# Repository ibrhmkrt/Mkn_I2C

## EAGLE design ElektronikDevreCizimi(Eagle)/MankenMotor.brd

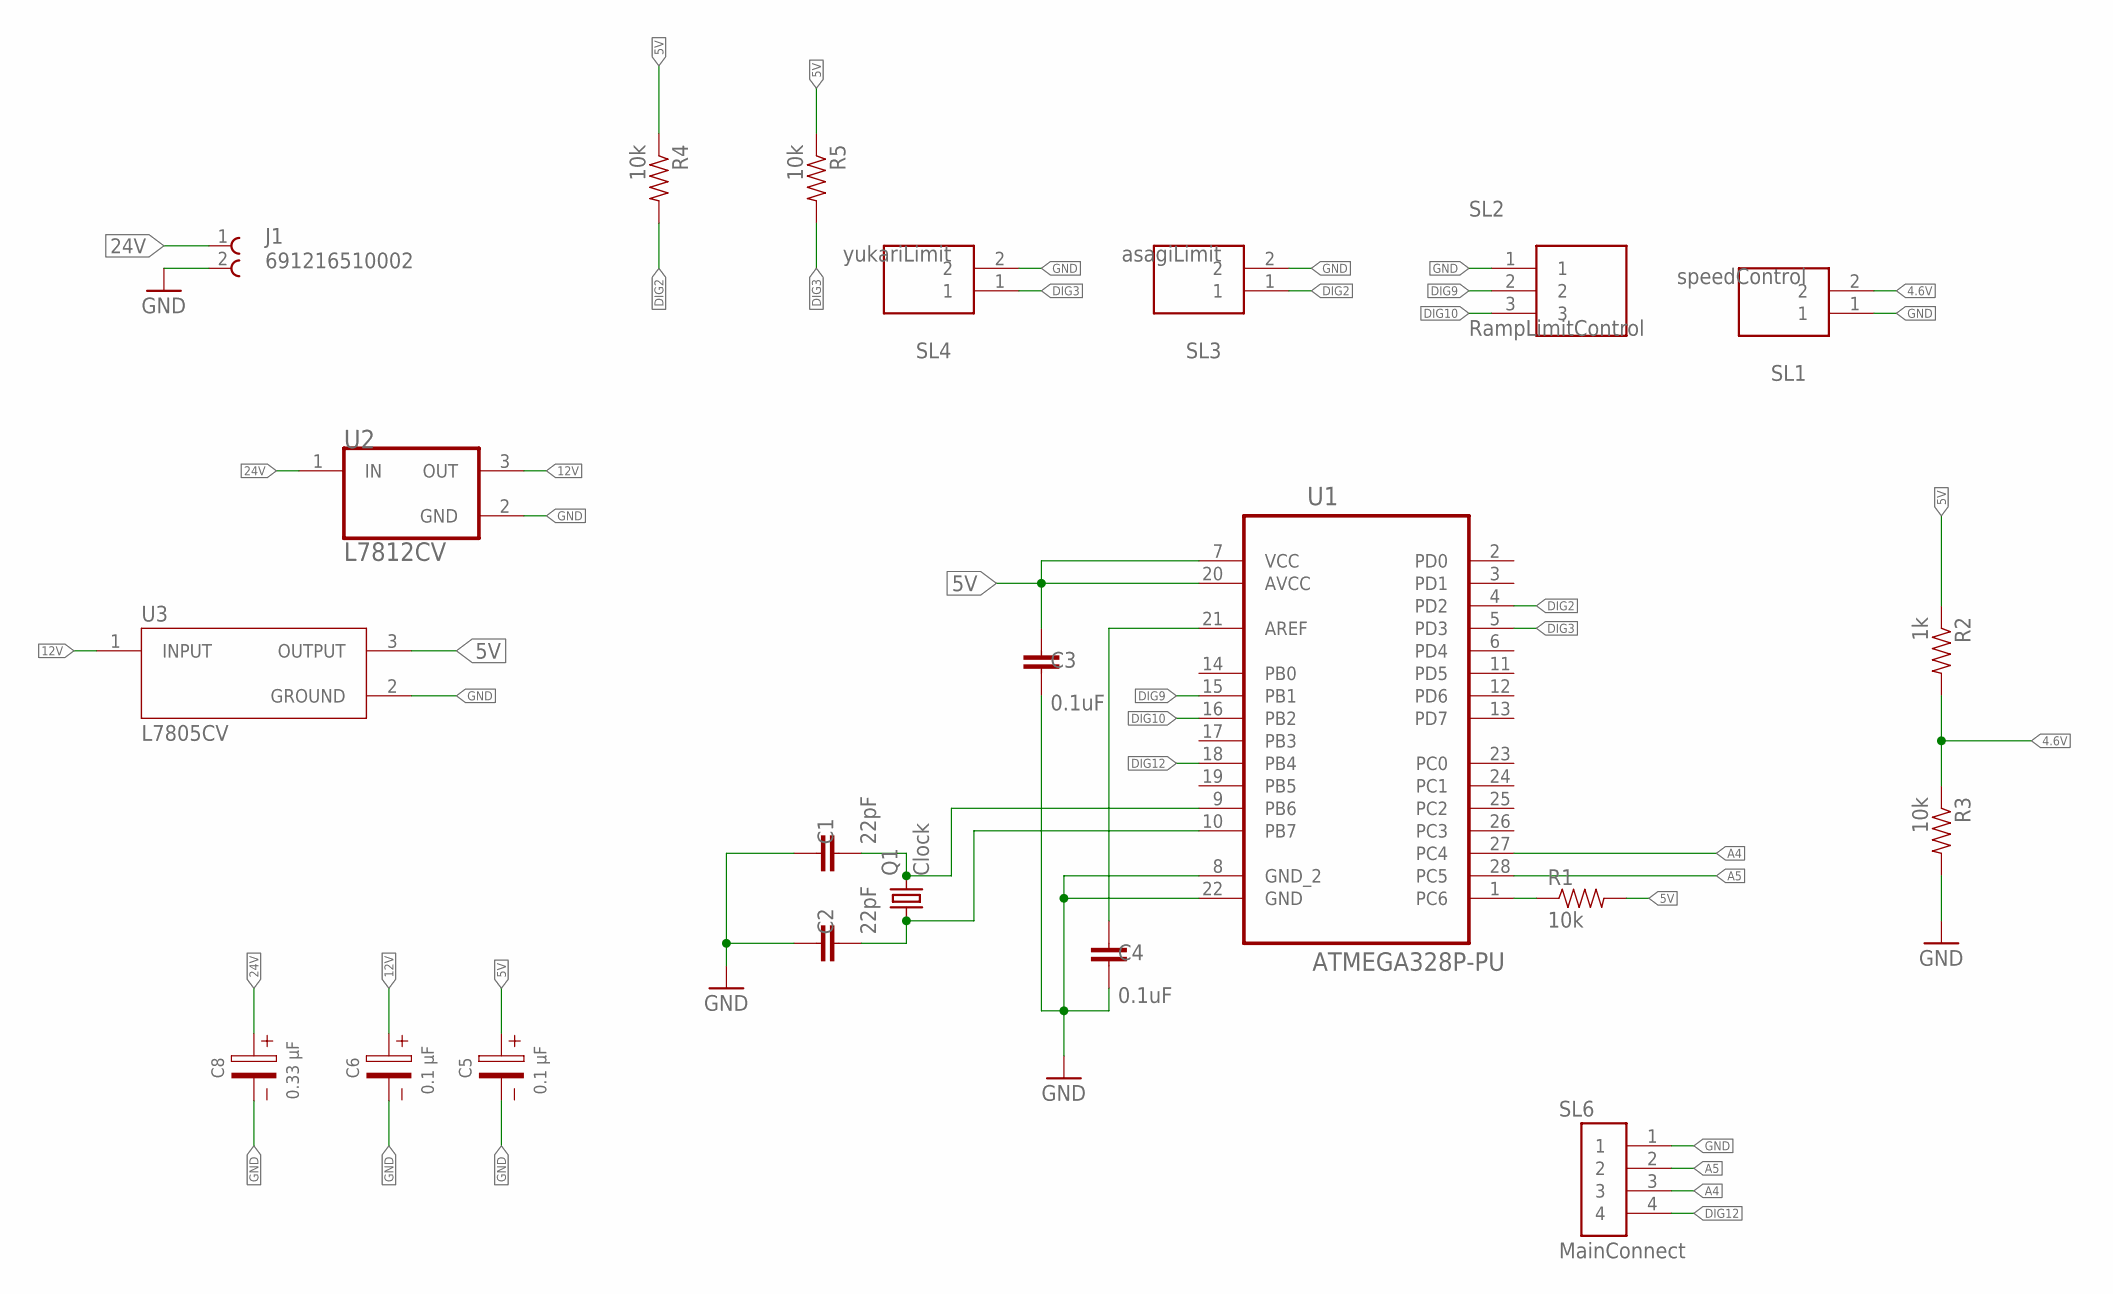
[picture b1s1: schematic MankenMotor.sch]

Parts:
C1, C2: 22pF; CAP-PTH-2.54
C3, C4: 0.1uF; CAP-PTH-SMALL-KIT
C5, C6: 0.1 µF; WCAP-ATG5_5X11(DXL)
C8: 0.33 µF; WCAP-ATG5_5X11(DXL)
J1: 691216510002
Q1: Clock; HC49/S
R1, R3, R4, R5: 10k; AXIAL-0.3
R2: 1k; AXIAL-0.3
SL1: speedControl; JST_B2B-XH-A(LF)(SN)
SL2: RampLimitControl; SHDR3W64P0X250_1X3_990X575X700
SL3: asagiLimit; JST_B2B-XH-A(LF)(SN)
SL4: yukariLimit; JST_B2B-XH-A(LF)(SN)
SL6: MainConnect; JST_B4B-XH-A(LF)(SN)
U1: ATMEGA328P-PU; DIP254P762X457-28
U2: L7812CV; TO-220-3
U3: L7805CV; TO255P1040X460X1968-3

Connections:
4.6V: R2.P$2 (2), R3.P$1 (1), SL1.2
5V: C3.1, C5.1 (+), R1.P$2 (2), R2.P$1 (1), R4.P$1 (1), R5.P$1 (1), U1.7 (VCC), U1.20 (AVCC), U3.3 (OUTPUT)
12V: C6.1 (+), U2.3 (OUT), U3.1 (INPUT)
24V: C8.1 (+), J1.1, U2.1 (IN)
A4: SL6.3, U1.27 (PC4)
A5: SL6.2, U1.28 (PC5)
DIG2: R4.P$2 (2), SL3.1, U1.4 (PD2)
DIG3: R5.P$2 (2), SL4.1, U1.5 (PD3)
DIG9: SL2.2, U1.15 (PB1)
DIG10: SL2.3, U1.16 (PB2)
DIG12: SL6.4, U1.18 (PB4)
GND: C1.1, C2.1, C3.2, C4.2, C5.2 (-), C6.2 (-), C8.2 (-), J1.2, R3.P$2 (2), SL1.1, SL2.1, SL3.2, SL4.2, SL6.1, U1.8 (GND_2), U1.22 (GND), U2.2 (GND), U3.2 (GROUND)
unnamed: R1.P$1 (1), U1.1 (PC6)
unnamed: C1.2, Q1.2, U1.9 (PB6)
unnamed: C2.2, Q1.1, U1.10 (PB7)
unnamed: C4.1, U1.21 (AREF)

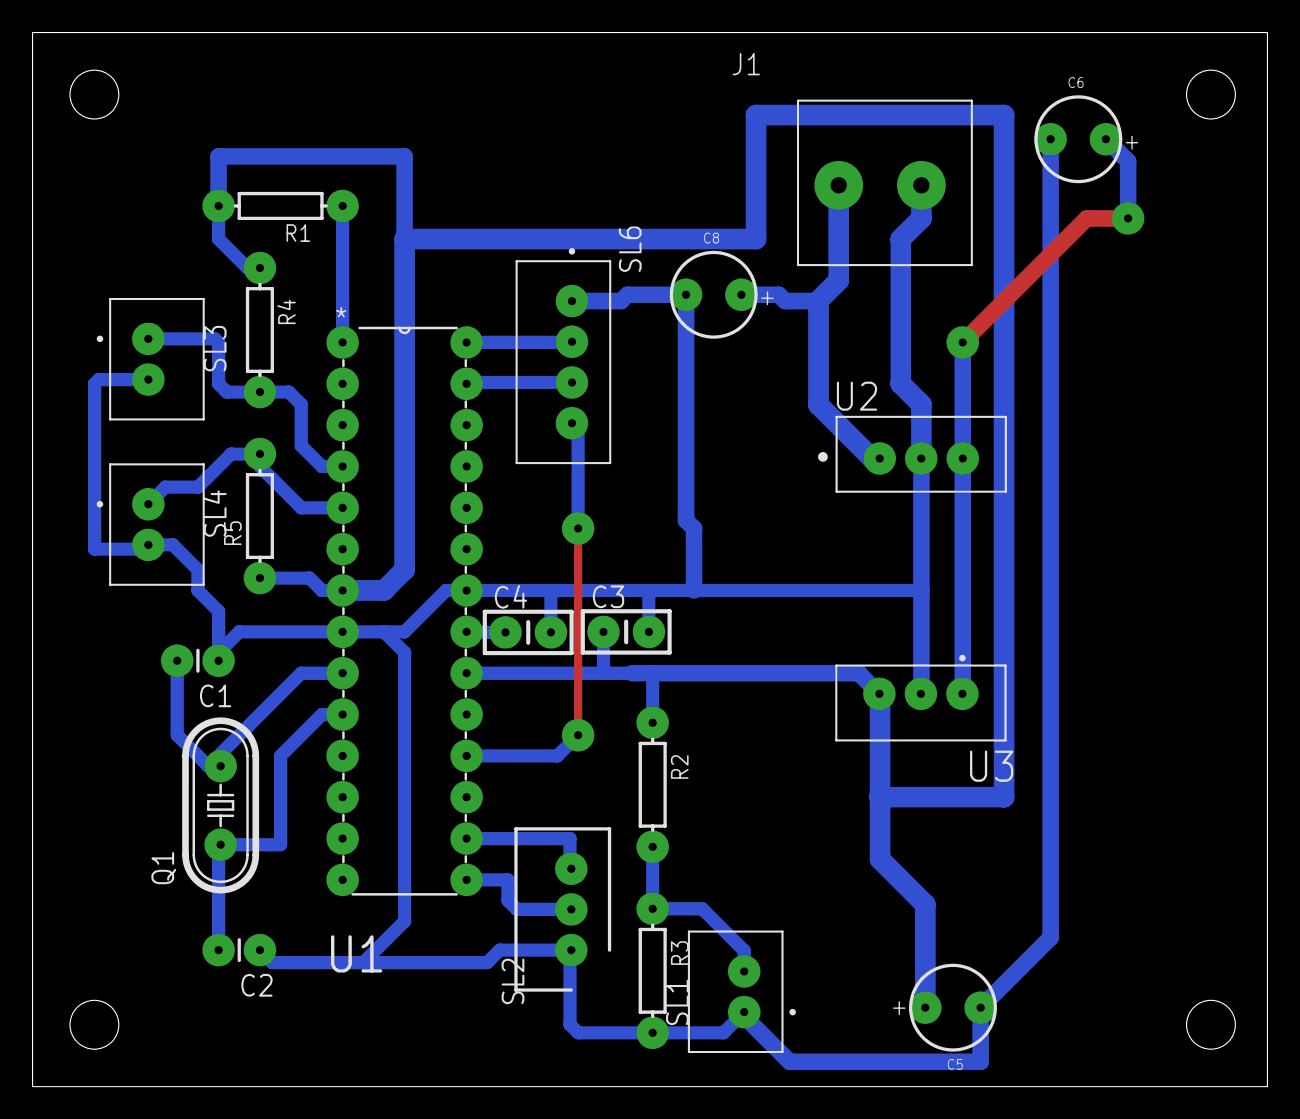
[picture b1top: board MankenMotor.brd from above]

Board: 2 copper layers, 75.9 x 64.8 mm, 22 parts (0 on the bottom side), 16 nets.

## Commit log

2020-02-20 Final
2020-02-20 Mkn_czm_pdf

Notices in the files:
parts and their libraries:
SparkFun-Resistors-1k: Licensing: Creative Commons ShareAlike 4.0 International - https://creativecommons.org/licenses/by-sa/4.0
Wurth_Capacitors_WCAP-ATG5-01uf-033uf: Copyright: Würth Elektronik
